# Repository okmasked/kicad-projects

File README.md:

# Engineering-projects
This is for my projects

# Tools used
tools used in these projects include:
  - NI Multisim
  - Kicad
  - Word (for documentation)

# Current Projects
- 03 Digitale Uhr

# Finished Projects
+ 02 LED-Herz Lm555
+ 01 LED-Beleuchtung (lost media)

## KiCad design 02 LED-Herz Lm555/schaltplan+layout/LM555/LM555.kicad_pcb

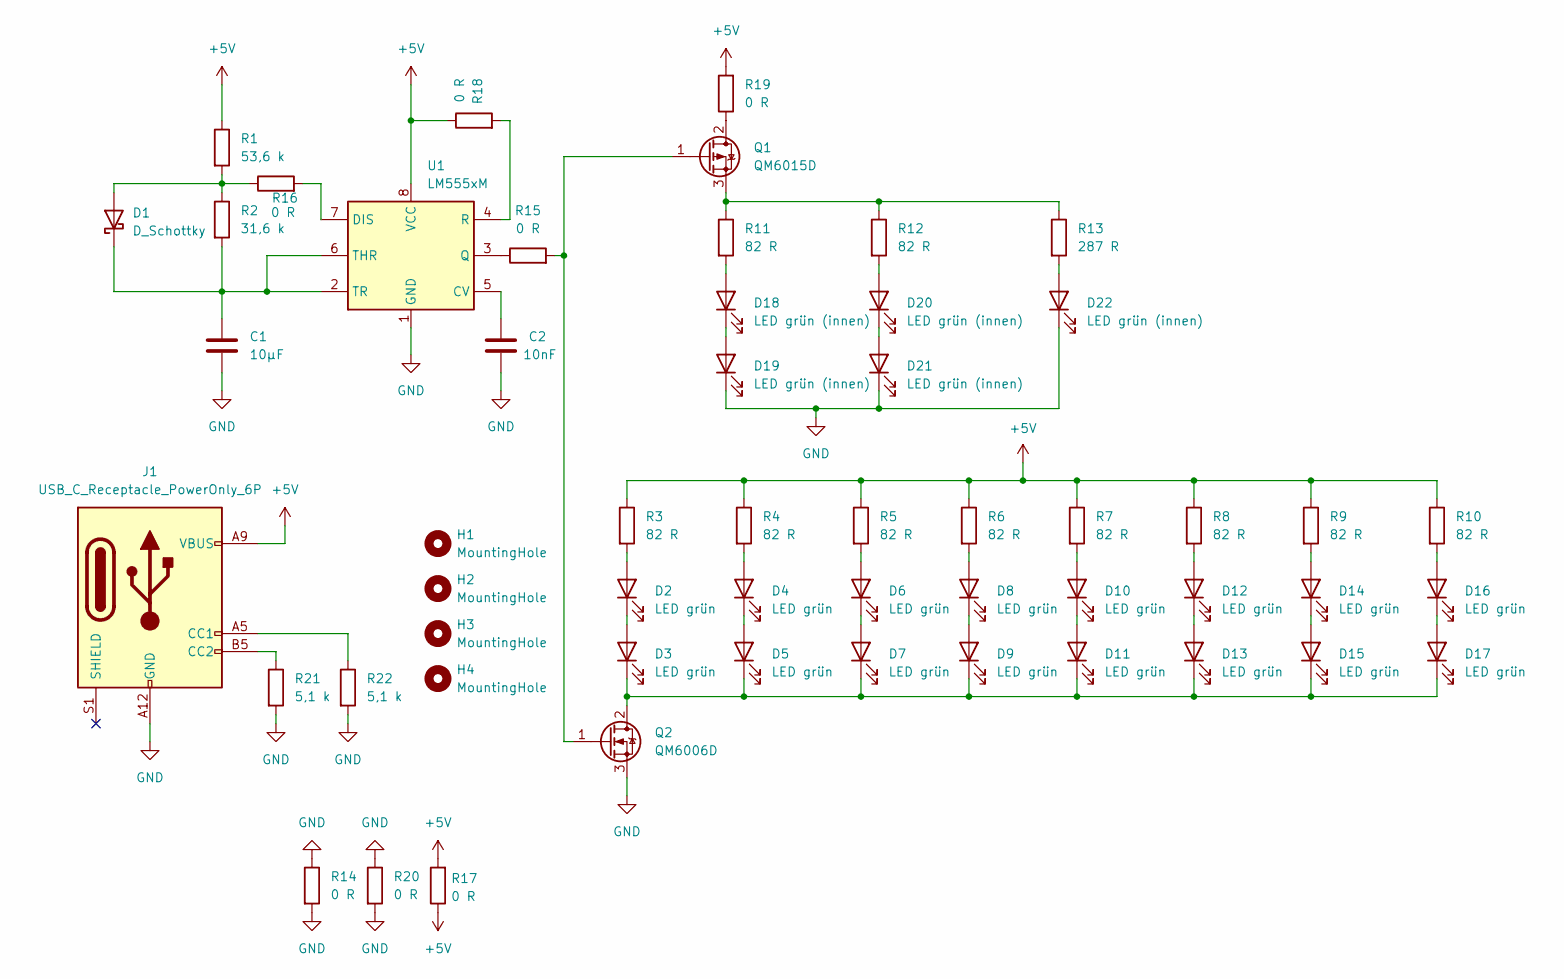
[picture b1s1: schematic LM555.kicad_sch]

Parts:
C1: 10µF; C_1206_3216Metric
C2: 10nF; C_1206_3216Metric
D1: D_Schottky; D_SOD-523
D2, D3, D4, D5, D6, D7, D8, D9, D10, D11, D12, D13, D14, D15, D16, D17: LED grün; LED_1206_3216Metric
D18, D19, D20, D21, D22: LED grün (innen); LED_1206_3216Metric
H1, H2, H3, H4: MountingHole; MountingHole_3mm
J1: USB_C_Receptacle_PowerOnly_6P; USB_C_Receptacle_GCT_USB4125-xx-x_6P_TopMnt_Horizontal
Q1: QM6015D; SOT-323_SC-70_Handsoldering
Q2: QM6006D; SOT-323_SC-70_Handsoldering
R1: 53,6 k; R_1206_3216Metric
R2: 31,6 k; R_1206_3216Metric
R3, R4, R5, R6, R7, R8, R9, R10, R11, R12: 82 R; R_1206_3216Metric
R13: 287 R; R_1206_3216Metric
R14, R15, R16, R17, R18, R19, R20: 0 R; R_1206_3216Metric
R21, R22: 5,1 k; R_1206_3216Metric
U1: LM555xM; SOIC-8_3.9x4.9mm_P1.27mm

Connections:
+5V: J1.A9 (VBUS), J1.B9 (VBUS), R1.1, R3.1, R4.1, R5.1, R6.1, R7.1, R8.1, R9.1, R10.1, R17.1, R17.2, R18.1, R19.2, U1.8 (VCC)
GND: C1.1, C2.1, D19.1 (K), D21.1 (K), D22.1 (K), J1.A12 (GND), J1.B12 (GND), Q2.3 (S), R14.1, R14.2, R20.1, R20.2, R21.2, R22.2, U1.1 (GND)
unnamed: D1.2 (A), R1.2, R2.1, R16.1
unnamed: C1.2, D1.1 (K), R2.2, U1.2 (TR), U1.6 (THR)
unnamed: D2.2 (A), R3.2
unnamed: D2.1 (K), D3.2 (A)
unnamed: D4.2 (A), R4.2
unnamed: D4.1 (K), D5.2 (A)
unnamed: D6.2 (A), R5.2
unnamed: D6.1 (K), D7.2 (A)
unnamed: D8.2 (A), R6.2
unnamed: D8.1 (K), D9.2 (A)
unnamed: D10.2 (A), R7.2
unnamed: D10.1 (K), D11.2 (A)
unnamed: D3.1 (K), D5.1 (K), D7.1 (K), D9.1 (K), D11.1 (K), D13.1 (K), D15.1 (K), D17.1 (K), Q2.2 (D)
unnamed: D12.2 (A), R8.2
unnamed: D12.1 (K), D13.2 (A)
unnamed: D14.2 (A), R9.2
unnamed: D14.1 (K), D15.2 (A)
unnamed: D16.2 (A), R10.2
unnamed: D16.1 (K), D17.2 (A)
unnamed: D18.2 (A), R11.2
unnamed: D18.1 (K), D19.2 (A)
unnamed: D20.2 (A), R12.2
unnamed: D20.1 (K), D21.2 (A)
unnamed: D22.2 (A), R13.2
unnamed: J1.A5 (CC1), R22.1
unnamed: J1.B5 (CC2), R21.1
unnamed: Q1.2 (D), R19.1
unnamed: Q1.1 (G), Q2.1 (G), R15.2
unnamed: Q1.3 (S), R11.1, R12.1, R13.1
unnamed: C2.2, U1.5 (CV)
unnamed: R16.2, U1.7 (DIS)
unnamed: R15.1, U1.3 (Q)
unnamed: R18.2, U1.4 (R)

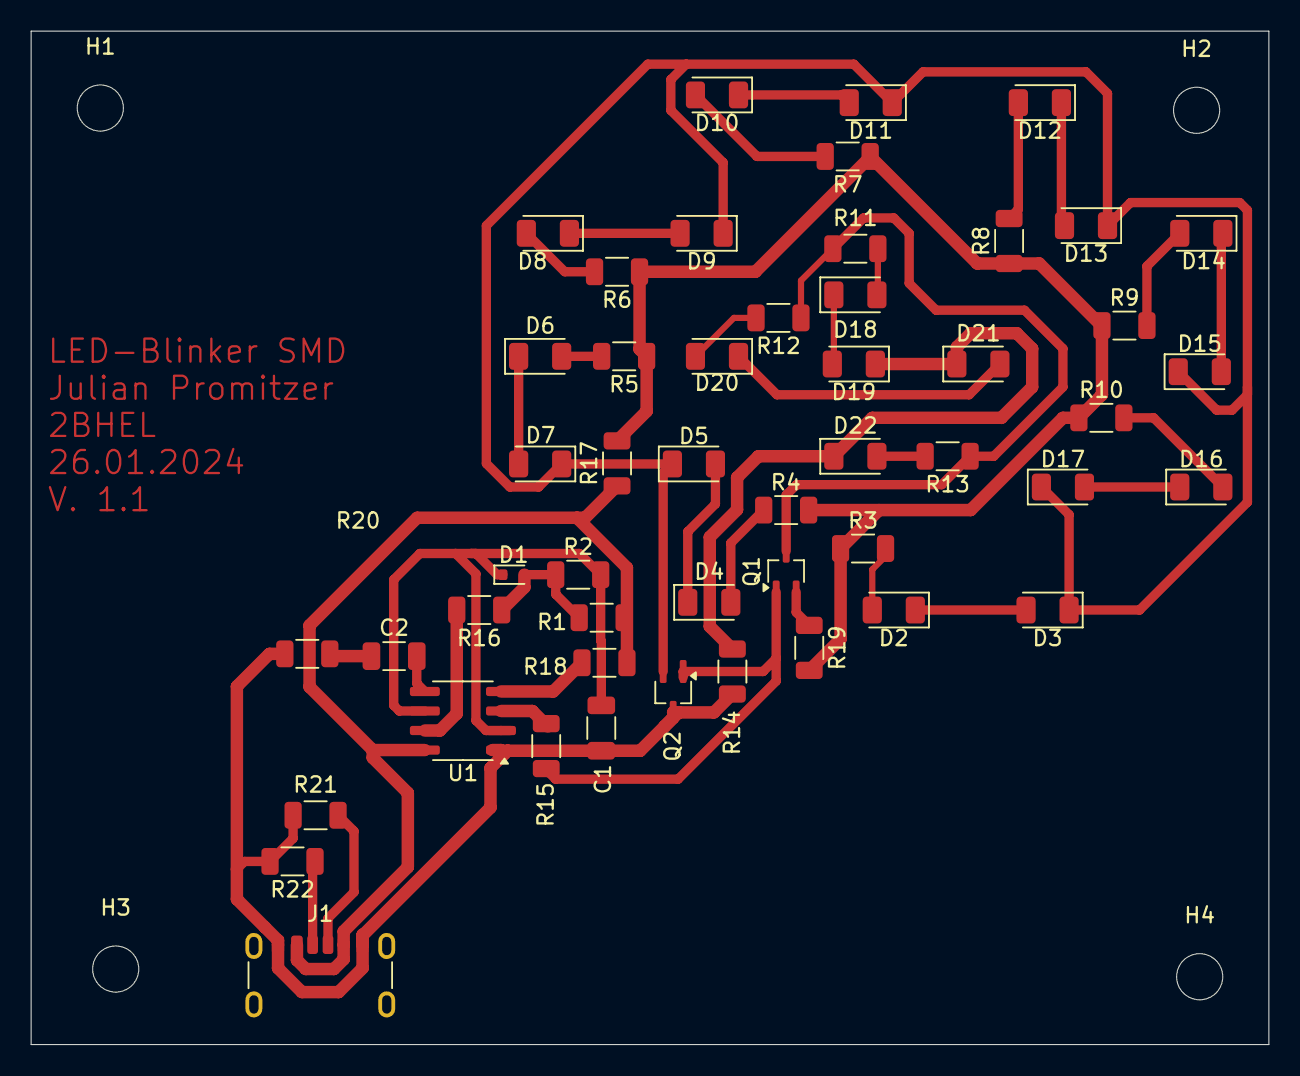
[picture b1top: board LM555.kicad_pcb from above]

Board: 2 copper layers, 80.5 x 65.9 mm, 54 parts (0 on the bottom side), 35 nets.

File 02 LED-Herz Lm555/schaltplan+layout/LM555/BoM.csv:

Reference;Value;Datasheet;Footprint;Stk;preis
C1;10µF;CL31B106KBHNNNE;Capacitor_SMD:C_1206_3216Metric;1;  0,30 
C2;10nF;CL31B103KHFNFNE;Capacitor_SMD:C_1206_3216Metric;1;  0,11 
D1;D_Schottky;BAS7002VH6327XTSA1;Diode_SMD:D_SOD-523;1;  0,22 
D2-D22;LED grün;B1591NG--20C000922U1930;LED_SMD:LED_1206_3216Metric;21;  2,52 
J1;USB_C;UJC-H-G-SMT-2-P6-TR;Connector_USB:USB_C_Receptacle_GCT_USB4125-xx-x_6P_TopMnt_Horizontal;1;  0,32 
Q1;QM6015D;NTS4101PT1G;Package_TO_SOT_SMD:SOT-323_SC-70_Handsoldering;1;  0,38 
Q2;QM6006D;2N7002WT1G;Package_TO_SOT_SMD:SOT-323_SC-70_Handsoldering;1;  0,18 
R1;53,6 k;RQ73C2B53K6BTD;Resistor_SMD:R_1206_3216Metric;1;  0,97 
R2;31,6 k;RQ73C2B31K6BTD;Resistor_SMD:R_1206_3216Metric;1;  0,97 
R3-R12;82 R;CRGCQ1206F82R;Resistor_SMD:R_1206_3216Metric;10;  0,42 
R13;287 R;RQ73C2B287RBTD;Resistor_SMD:R_1206_3216Metric;1;  0,84 
R14-R20;0 R;CRG1206ZR;Resistor_SMD:R_1206_3216Metric;7;  0,70 
U1;LM555xM;LM555CM/NOPB;Package_SO:SOIC-8_3.9x4.9mm_P1.27mm;1;  1,15 
;;;;;  9,08

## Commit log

2025-01-29 Added 02 LED-Herz Lm555
    Projekt von Hwe das zum fertigen war bis zum 27.01.2025
2025-02-28 added 03 Digitale Uhr to repo
2025-05-23 set to current progress
2025-05-23 fixed 03 Digitale Uhr/README.md
2025-05-23 fixed 03 digitale Uhr/README.md for real now
